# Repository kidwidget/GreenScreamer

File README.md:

# GreenScreamer
Guitar Effects Pedal
Uses Kicad
Has extra mounting holes for all capacitors, resistors, and diodes that effect tone. This is so you can solder in female pin headers to test various combinations before commiting. Bottom layer is only for ground plane. It can be omitted if you are making a single sided PCB. This will need jumper wires, refer to picture of finished product.

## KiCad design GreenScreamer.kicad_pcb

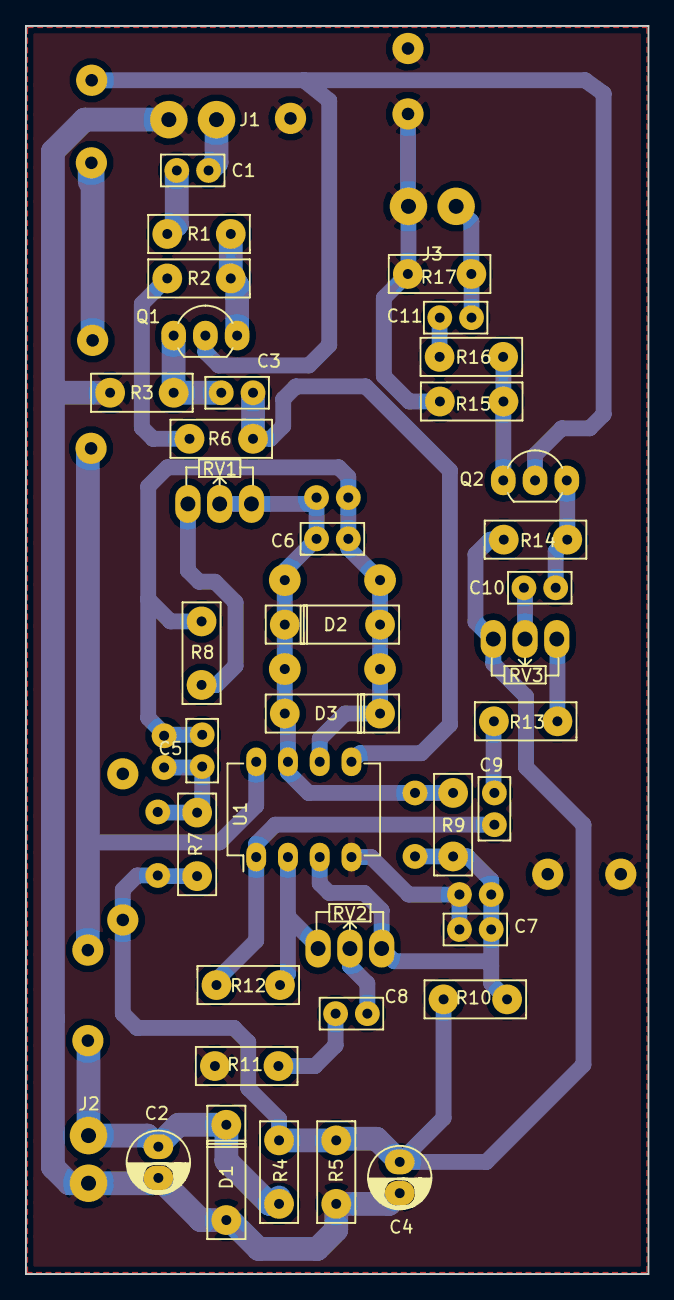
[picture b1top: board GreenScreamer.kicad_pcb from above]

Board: 2 copper layers, 49.8 x 99.8 mm, 40 parts (0 on the bottom side), 24 nets.

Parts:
C1: .027uF; Capacitor1
C2: 100uF; C_Radial_D5_L6_P2.5
C3, C9: 1uF; Capacitor1
C4: 47uF; C_Radial_D5_L6_P2.5
C5: .047uF; Capacitor1
C6: 51pF; Capacitor1
C7, C8: .22uf Tant; Capacitor1
C10: .1uF; Capacitor1
C11: 10uF; Capacitor1
D1: 1N4003; diode3
D2, D3: 1N914; diode3
J1, J2, J3: JackMono; MonoJackRemote
Q1, Q2: KSC1518; TO-92_Inline_Wide_Oval
R1, R9, R12, R13: 1k; Resistor2
R2, R14: 510k; Resistor2
R3, R4, R5, R6, R10, R15, R17: 10k; Resistor2
R7: 4.7k; Resistor2
R8: 51k; Resistor2
R11: 220; Resistor2
R16: 100; Resistor2
RV1: 500k; Potentiometer_WirePads_Small_Oval
RV2: 20k; Potentiometer_WirePads_Small_Oval
RV3: 100k; Potentiometer_WirePads_Small_Oval
U1: JNR4558; DIP-8_W7.62mm_LongPads

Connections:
+9V: C2.1, D1.1, J2.1, Q1.2, Q2.2, R4.1, U1.8
/4v5: C4.1, R2.2, R4.2, R5.1, R6.2, R7.2, R10.2, R14.1, RV3.3
GNDREF: C2.2, C4.2, C7.2, D1.2, J1.2, J2.2, J3.2, R3.2, R5.2, R11.2, R15.1, R17.1, U1.4
unnamed: C1.1, R1.2
unnamed: C1.2, J1.1
unnamed: C3.1, R6.1, U1.5
unnamed: C3.2, Q1.1, R3.1
unnamed: C5.1, R7.1
unnamed: C5.2, C6.2, D2.2, D3.1, R8.2, U1.6
unnamed: C6.1, D2.1, D3.2, R9.2, RV1.2, RV1.3, U1.7
unnamed: C7.1, R9.1, R10.1, RV2.3, U1.3
unnamed: C8.1, RV2.2
unnamed: C8.2, R11.1
unnamed: C9.1, R13.2
unnamed: C9.2, R12.1, U1.1
unnamed: C10.1, Q2.3, R14.2
unnamed: C10.2, RV3.2
unnamed: C11.1, R16.2
unnamed: C11.2, J3.1, R17.2
unnamed: Q1.3, R1.1, R2.1
unnamed: Q2.1, R15.2, R16.1
unnamed: R8.1, RV1.1
unnamed: R12.2, RV2.1, U1.2
unnamed: R13.1, RV3.1
